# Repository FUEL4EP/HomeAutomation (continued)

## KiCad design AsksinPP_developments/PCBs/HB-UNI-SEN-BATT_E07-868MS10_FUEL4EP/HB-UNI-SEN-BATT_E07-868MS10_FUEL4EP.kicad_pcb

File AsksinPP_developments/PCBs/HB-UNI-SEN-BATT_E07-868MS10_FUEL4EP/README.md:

# HB-UNI-SEN-BATT_E07-868MS10_FUEL4EP  

**Platine für DIY AsksinPP Projekte basierend auf den folgenden möglichen Arduino-Modulen:**
- [Arduino Pro Mini 328 - 3.3V/8MHz](https://www.sparkfun.com/arduino-pro-mini-328-3-3v-8mhz.html): 32kByte Programmspeicher, 4kByte SRAM, 1kByte EEPROM
- NEU: [HB_Pro_Mini_ATMEGA1284P_FUEL4EP](https://github.com/FUEL4EP/HomeAutomation/tree/master/AsksinPP_developments/PCBs/HB_Pro_Mini_ATMEGA1284P_FUEL4EP)
	+ mit deutlich mehr Programm-, RAM- und EEPROM-Speicher als Arduino Pro Mini: 128kByte Programmspeicher, 16kByte SRAM, 4kByte EEPROM)
- [Tindie Pro Mini XL - v2 - ATmega 1284p](https://www.tindie.com/products/prominimicros/pro-mini-xl-v2-atmega-1284p/)
	+ mit deutlich mehr Programm-, RAM- und EEPROM-Speicher als Arduino Pro Mini: 128kByte Programmspeicher, 16kByte SRAM, 4kByte EEPROM)

## Credits

- diese Platine ist von Alexander Reinerts Platine [HB-UNI-SEN-BATT](https://github.com/alexreinert/PCB/tree/master/HB-UNI-SEN-BATT) abgeleitet.
- vielen Dank an Alexander Reinert für die Vorarbeit.

## Status der Validierung der Platine

- Platine wurde bis zur Version V1.3 bei JLCPCB erfolgreich gefertigt und validiert
- der Prototyp der neuen Platinenversion V1.4 wurde bei JLCPCB gefertigt, von Hand bestückt, verlötet und erfolgreich mit dem Sketch [HB-UNI-SENSOR1-AQ-BME680_KF_rLF](https://github.com/FUEL4EP/HomeAutomation/tree/master/AsksinPP_developments/sketches/HB-UNI-Sensor1-AQ-BME680_KF_rLF) validiert:
	
- Als Funkmodul wurde der [Adapter_EByte_E07_900MM10S_to_Ebyte_E07_868MS10_FUEL4EP](https://github.com/FUEL4EP/HomeAutomation/tree/master/AsksinPP_developments/PCBs/Adapter_EByte_E07_900MM10S_to_Ebyte_E07_868MS10_FUEL4EP) verwendet.

## Eigenschaften

- Weiterentwicklung von [HB-UNI-SEN-BATT](https://github.com/alexreinert/PCB/tree/master/HB-UNI-SEN-BATT) mit denselben Außenmaßen
- neue Eigenschaften:
	+ alternativ werden verschiedene Arduino Module unterstützt:
		- [Arduino Pro Mini 328 - 3.3V/8MHz](https://www.sparkfun.com/arduino-pro-mini-328-3-3v-8mhz.html): 32kByte Programmspeicher, 4kByte SRAM, 1kByte EEPROM
		- [HB_Pro_Mini_ATMEGA1284P_FUEL4EP](https://github.com/FUEL4EP/HomeAutomation/tree/master/AsksinPP_developments/PCBs/HB_Pro_Mini_ATMEGA1284P_FUEL4EP)
			+ mit deutlich mehr Programm-, RAM- und EEPROM-Speicher als Arduino Pro Mini: 128kByte Programmspeicher, 16kByte SRAM, 4kByte EEPROM)
			+ mit optionalem Boost-Konverter für Betrieb mit NiMH-Akkumulatoren oder nur einer AA Alkaline Battterie
		- [Tindie Pro Mini XL - v2 - ATmega 1284p](https://www.tindie.com/products/prominimicros/pro-mini-xl-v2-atmega-1284p/)
			+ mit deutlich mehr Programm-, RAM- und EEPROM-Speicher als Arduino Pro Mini: 128kByte Programmspeicher, 16kByte SRAM, 4kByte EEPROM

    + nur eine LED
    + dafür optionale Unterstützung von Akkumulatorbetrieb mit einem externen 'Huckepack' Aufwärtswandlermodul (siehe z.B. [HB-UNI-SENSOR1-CO2-SCD30](https://github.com/FUEL4EP/HomeAutomation/tree/master/AsksinPP_developments/sketches/HB-UNI-Sensor1-CO2_SCD30)
    + Stiftleiste J10 mit Versorgungsspannungen zum Gehäuseoberteil oder Akkulademodul
    + Korrektur der Abstandfehlers bei einem Batteriehalter. Beim [HB-UNI-SEN-BATT](https://github.com/alexreinert/PCB/tree/master/HB-UNI-SEN-BATT) hat das schon mal gerne zu thermischen Ausfällen durch mechanische Spannungen geführt.

### Benötigte Bauteile:
* eines der folgenden Arduino Module
	- [Arduino Pro Mini 328 - 3.3V/8MHz](https://www.sparkfun.com/arduino-pro-mini-328-3-3v-8mhz.html)
	- [HB_Pro_Mini_ATMEGA1284P_FUEL4EP](https://github.com/FUEL4EP/HomeAutomation/tree/master/AsksinPP_developments/PCBs/HB_Pro_Mini_ATMEGA1284P_FUEL4EP)
	- [Tindie Pro Mini XL - v2 - ATmega 1284p](https://www.tindie.com/products/prominimicros/pro-mini-xl-v2-atmega-1284p/)
*  [eByte E07-868MS10 Sendemodul 868MHz](https://www.elecbee.com/de-24376-E07-868MS10-CC1101-Stamp-Hole-Antenna-IoT-UHF-1000m-868MHz-SPI-10dBm-Wireless-Transmitter-Transceiver-RF-Module) oder alternativ das [Elecbee CC1101 Wireless-Modul 868 MHz](https://www.elecbee.com/de-24507-CC1101-Wireless-Module-868MHz-Digital-Transmission-Receiving-Industrial-grade-RF-Communication-Transparent-Transmission) Modul
* 1x LEDs 3mm Low Current (Pin 4)
* 1x 470Ohm Widerstände (Vorwiderstand für LED)
* Elko 10uF 1,5mm
* 2x Keystone 2460 Batteriehalter 1xAA (oder Goobay 1xAA Batteriehalter)
* Mikroschalter 6*6mm
* Stiftleiste RM 1.27mm 1x8 Pin (für eByte E07-868MS10 Modul)
* Stiftleisten RM 2,54mm (nach Bedarf)
* IRLU024N (optional für Verpolungsschutz)
* 100KOhm Widerstand (optional für Verpolungsschutz)
* 2x 10KOhm Widerstand (Pullup für I2C)

### Aufbauhinweise

- es wird dringend angeraten, vor dem Einbau der I2C Sensoren durchzuführen
    + einen Frequenztest. Hier der Frequenztest für einen [Tindie Pro Mini XL - v2 - ATmega 1284p](https://www.tindie.com/products/prominimicros/pro-mini-xl-v2-atmega-1284p/) : [FreqTest_1284P.ino](../Supplements/FreqTest_1284P/FreqTest_1284P.ino)
    + einen Leckstromtest. Hier der Leckstromtest für einen [Tindie Pro Mini XL - v2 - ATmega 1284p](https://www.tindie.com/products/prominimicros/pro-mini-xl-v2-atmega-1284p/) : [SleepTest_1284P.ino](../Supplements/SleepTest_1284P/SleepTest_1284P.ino)
        + der Leckstrom im Sleepmode sollte < 10 uA betragen
    + für einen Arduino Pro Mini die entsprechenden Standardsketche für den Frequenztest und den SleepTest verwenden.
    + am besten diese beiden Tests in einem Testaufbau mit Stecksockeln vor dem Einlöten durchführen

## Konfiguration der Überbrückungen

- bitte die Platinenüberbrückungen vor Inbetriebnahme je nach gewählter Hardwarekonfiguration wählen:

- die Tabellen dazu sind [hier](./Jumper_settings) zu finden
    
## lokale Installation des Github Releases auf Deinem Computer

- gehe bitte in Dein Zielinstallationsverzeichnis, wo Du mit der HB-UNI-SEN-BATT_E07-868MS10_FUEL4EP Platine mit KiCAD arbeiten möchtest

  - gebe dort 'git clone https://github.com/FUEL4EP/HomeAutomation.git' ein
	  + damit lädst Du mein [Sammelrepository](https://github.com/FUEL4EP/HomeAutomation) für alle meine auf Github freigegebenen HomeBrew Entwicklungen herunter.
  - dann findest Du ein neues Verzeichnis 'HomeAutomation' auf Deinem Rechner, das alle meine auf Github freigebenen Entwicklungen enthält, siehe [README.md](https://github.com/FUEL4EP/HomeAutomation/blob/master/README.md)
  	+ mache bitte regelmäßig ein Update mit 'git pull'
 -	die Platine HB-UNI-SEN-BATT_E07-868MS10_FUEL4EP findest Du unter './HomeAutomation/tree/master/AsksinPP_developments/PCBs/HB-UNI-SEN-BATT_E07-868MS10_FUEL4EP'
 
- alternativ kann vom Github [Sammelrepository](https://github.com/FUEL4EP/HomeAutomation) die ZIP-Datei HomeAutomation-master.zip heruntergeladen und auf dem lokalen Rechner ausgepackt werden. Bitte dann regelmäßig auf Github nach Updates schauen.

### Passende AsksinPP Projekte von FUEL4EP
- Arduino Pro Mini ATMega328P oder Tindie Pro Mini XL - v2 - ATmega 1284p basierend:
    + [HB-UNI-Sensor1-THPD-BME280](https://github.com/FUEL4EP/HomeAutomation/tree/master/AsksinPP_developments/sketches/HB-UNI-Sensor1-THPD-BME280)
    + [HB-UNI-Sensor1-TH-SHT75](https://github.com/FUEL4EP/HomeAutomation/tree/master/AsksinPP_developments/sketches/HB-UNI-Sensor1-TH-SHT75)
     + [HB-UNI-Sensor1-CO2_SCD30](https://github.com/FUEL4EP/HomeAutomation/tree/master/AsksinPP_developments/sketches/HB-UNI-Sensor1-CO2_SCD30)
- [HB_Pro_Mini_ATMEGA1284P_FUEL4EP](https://github.com/FUEL4EP/HomeAutomation/tree/master/AsksinPP_developments/PCBs/HB_Pro_Mini_ATMEGA1284P_FUEL4EP) oder [Tindie Pro Mini XL - v2 - ATmega 1284p](https://www.tindie.com/products/prominimicros/pro-mini-xl-v2-atmega-1284p/) basierend:
     + [HB-UNI-Sensor1-AQ-BME680](https://github.com/FUEL4EP/HomeAutomation/tree/master/AsksinPP_developments/sketches/HB-UNI-Sensor1-AQ-BME680)
    + [HB-UNI-Sensor1-AQ-BME680_KF](https://github.com/FUEL4EP/HomeAutomation/tree/master/AsksinPP_developments/sketches/HB-UNI-Sensor1-AQ-BME680_KF)
    + [HB-UNI-Sensor1-AQ-BME680_KF_DEBUG](https://github.com/FUEL4EP/HomeAutomation/tree/master/AsksinPP_developments/sketches/HB-UNI-Sensor1-AQ-BME680_KF_DEBUG)
    + [HB-UNI-Sensor1-RAD-AL53](https://github.com/FUEL4EP/HomeAutomation/tree/master/AsksinPP_developments/sketches/HB-UNI-Sensor1-RAD-AL53)
    + [HB-UNI-Sensor1-THPD-SHT85](https://github.com/FUEL4EP/HomeAutomation/tree/master/AsksinPP_developments/sketches/HB-UNI-Sensor1-THPD-SHT85)

### Passendes Gehäuse
* Camdenboss CBRS01SWH und CBRS01VWH
* oder [Gehäuse HB-UNI-SEN-BATT snap in V2 von wpatrick](https://www.thingiverse.com/thing:3540481) für 3D-Druck

### Hinweise
* Achtung: Kein Überspannungschutz vorhanden
* der Verpolungsschutz ist optional. Dafür Bauteil Q1 (IRLU024N) und R3 (100KOhm Widerstand) bestücken. Alternativ JP1 auf der Platinenrückseite überbrücken, um ohne Verpolungsschutz zu arbeiten.

### KiCAD Plugin
- für die Erzeugung der JLCPCB Produktionsdaten wurde das Plugin [KiCAD JLCPCB tools](https://github.com/bouni/kicad-jlcpcb-tools) verwendet.

## Bestellen von Platinen

- die Platine kann entweder direkt bei JLCPCB bestellt werden
- die notwendigen Produktionsdaten stehen [hier](./jlcpcb/production_files/)
- oder per PN bei [FUEL4EP](https://homematic-forum.de/forum/ucp.php?i=pm&mode=compose&u=20685) im Homematic Forum nachfragen. Aus der Bestellung der Prototypen sind noch Platinen kostengünstig abzugeben (Stand 13. Juli 2023).
	
## passende DIY I2C-Sensormodule für die Fertigung bei JLCPCB
- als DIY-Ersatz für kommerzielle Sensormodule stehen folgende passende Adapterplatinen zur Verfügung:
	- [I2C_Module_BME280_FUEL4EP](https://github.com/FUEL4EP/HomeAutomation/tree/master/AsksinPP_developments/PCBs/I2C_Module_BME280_FUEL4EP)
	- [I2C_Module_BME680_FUEL4EP](https://github.com/FUEL4EP/HomeAutomation/tree/master/AsksinPP_developments/PCBs/I2C_Module_BME680_FUEL4EP)
	- [I2C_Module_SHT85_BME280_FUEL4EP](https://github.com/FUEL4EP/HomeAutomation/tree/master/AsksinPP_developments/PCBs/I2C_Module_SHT85_BME280_FUEL4EP)
	- [I2C_Module_SHT45_BME280_FUEL4EP](https://github.com/FUEL4EP/HomeAutomation/tree/master/AsksinPP_developments/PCBs/I2C_Module_SHT45_BME280_FUEL4EP)
	- [4Bit_I2C_Port_Expander_Module_FUEL4EP](https://github.com/FUEL4EP/HomeAutomation/tree/master/AsksinPP_developments/PCBs/4Bit_I2C_Port_Expander_Module_FUEL4EP)

## Versionen
- KiCad Schaltplan-Editor Version: 8.0.9-8.0.9-0~ubuntu22.04.1, release build unter Kubuntu22.04.1
- KiCad Leiterplatteneditor Version: 8.0.9-8.0.9-0~ubuntu22.04.1, release build unter Kubuntu22.04.1 1.
- aktuelle PCB Version 1.4 
- aktuelle Schematics Version 1.3 

## Disclaimer

-  die Nutzung der hier veröffentlichten Inhalte erfolgt vollständig auf eigenes Risiko und ohne jede Gewähr.

## Lizenz 

**Creative Commons BY-NC-SA**<br>
Give Credit, NonCommercial, ShareAlike

<br />This work is licensed under a <a rel="license" href="http://creativecommons.org/licenses/by-nc-sa/4.0/">Creative Commons Attribution-NonCommercial-ShareAlike 4.0 International License</a>.

-EOF

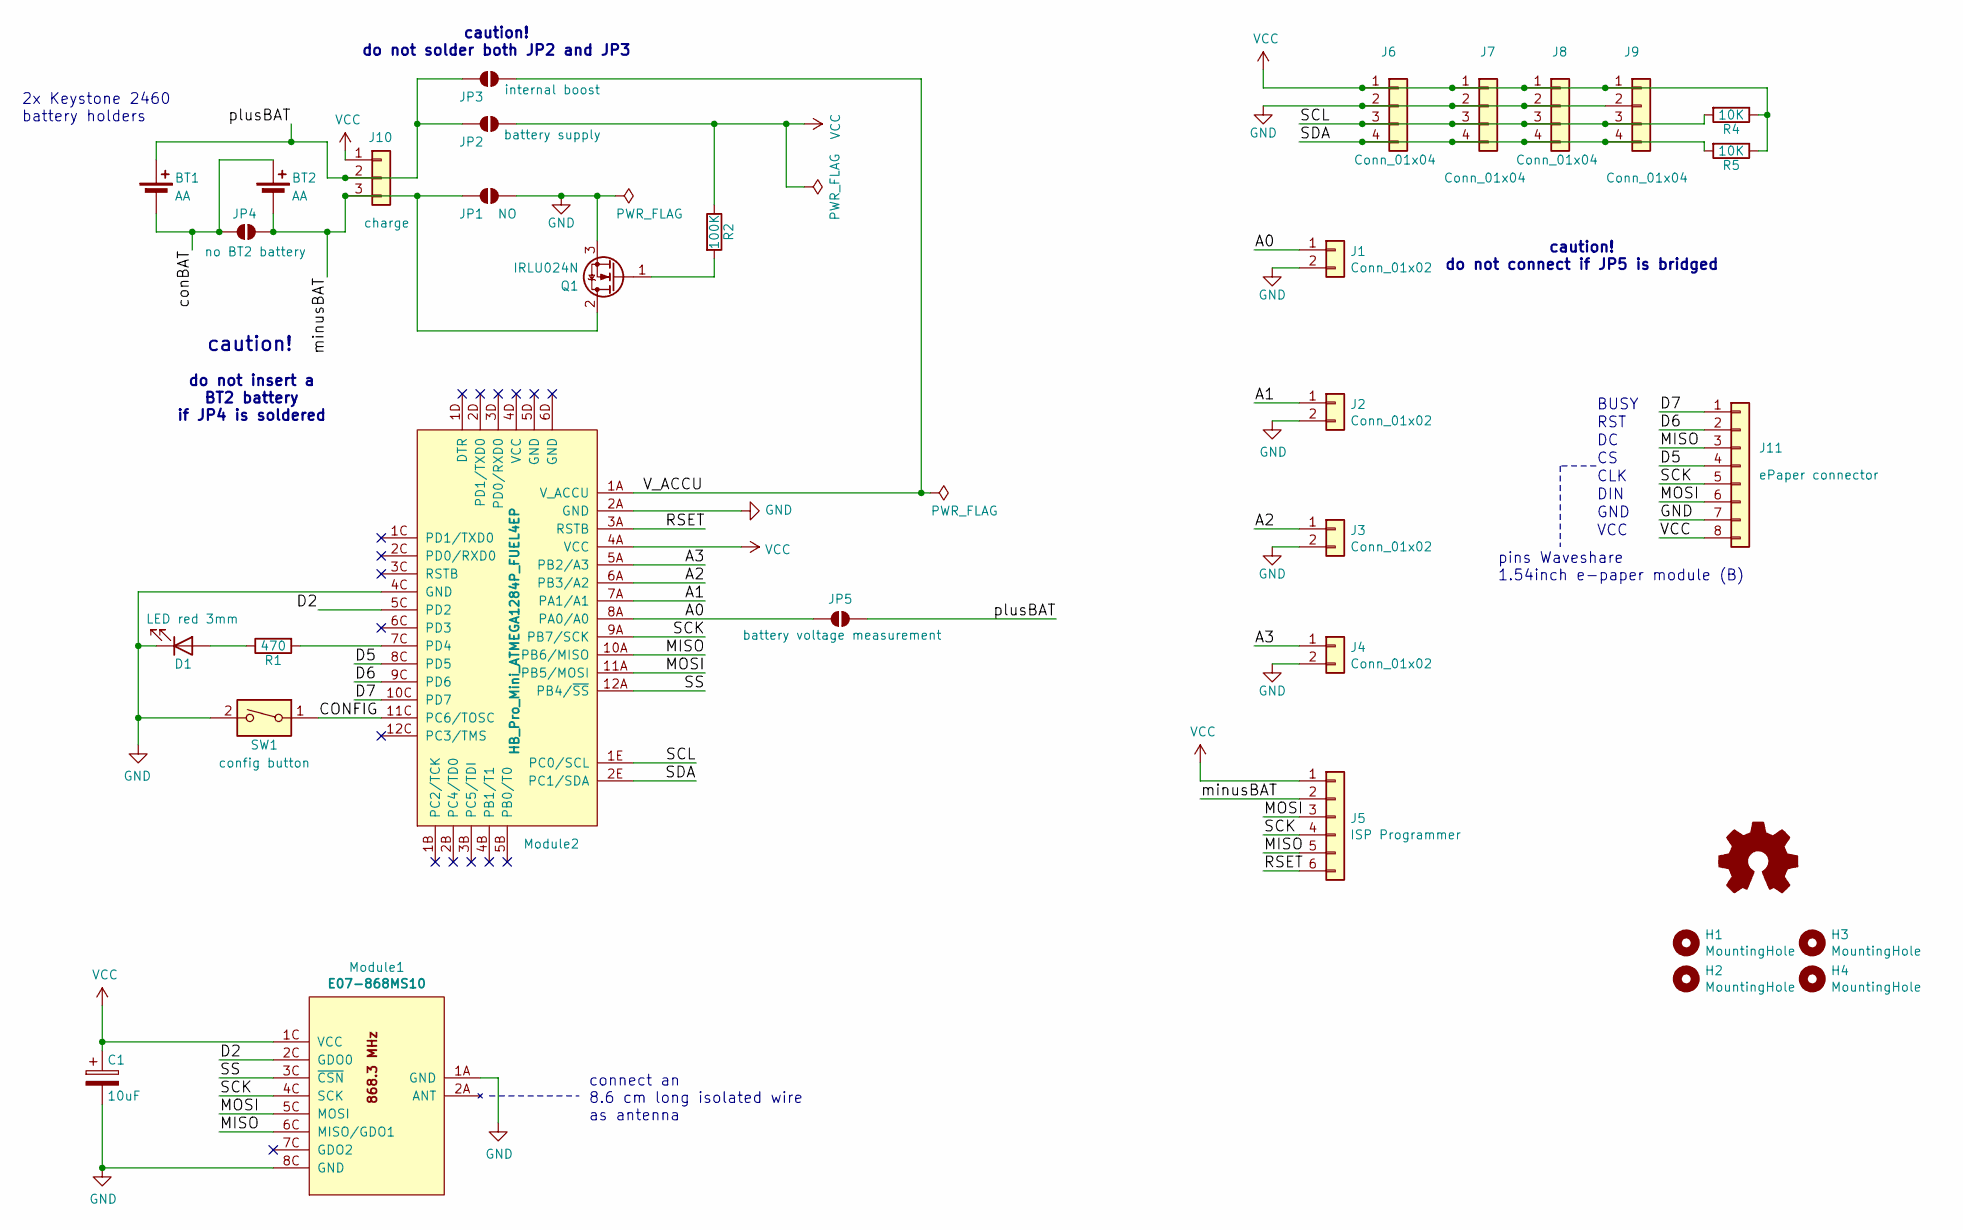
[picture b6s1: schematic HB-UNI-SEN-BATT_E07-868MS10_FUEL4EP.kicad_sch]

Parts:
BT1, BT2: AA; BatteryHolder_Keystone_2460_1xAA
C1: 10uF; CP_Radial_D4.0mm_P1.50mm
D1: LED red 3mm; LED_D3.0mm
H1, H2, H3, H4: MountingHole; MountingHole_2.2mm_M2_Pad_Via
J1, J2, J3, J4: Conn_01x02; PinHeader_1x02_P2.54mm_Vertical
J5: ISP Programmer; PinHeader_1x06_P2.54mm_Vertical
J6, J7, J8, J9: Conn_01x04; PinHeader_1x04_P2.54mm_Vertical
J10: charge; PinHeader_1x03_P2.54mm_Vertical
J11: ePaper connector; PinPads_1x08_P2.00mm_Vertical
JP1: NO; SolderJumper-2_P1.3mm_Open_Pad1.0x1.5mm
JP2: battery supply; SolderJumper-2_P1.3mm_Open_Pad1.0x1.5mm
JP3: internal boost; SolderJumper-2_P1.3mm_Open_Pad1.0x1.5mm
JP4: no BT2 battery; SolderJumper-2_P1.3mm_Open_Pad1.0x1.5mm
JP5: battery voltage measurement; SolderJumper-2_P1.3mm_Open_Pad1.0x1.5mm
LOGO1: Logo_Open_Hardware_Small; CC-BY-ND-SA
Module1: E07-868MS10; eByte_E07-868MS10
Module2: HB_Pro_Mini_ATMEGA1284P_FUEL4EP
Q1: IRLU024N; TO-251-3_Vertical
R1: 470; R_Axial_DIN0207_L6.3mm_D2.5mm_P2.54mm_Vertical
R2: 100K; R_Axial_DIN0207_L6.3mm_D2.5mm_P2.54mm_Vertical
R4, R5: 10K; R_Axial_DIN0207_L6.3mm_D2.5mm_P2.54mm_Vertical
SW1: config button; SW_PUSH_6mm_H5mm

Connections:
/A0: J1.1, JP5.1 (A), Module2.8A (PA0/A0)
/A1: J2.1, Module2.7A (PA1/A1)
/A2: J3.1, Module2.6A (PB3/A2)
/A3: J4.1, Module2.5A (PB2/A3)
/CONFIG: Module2.11C (PC6/TOSC), SW1.1
/D2: Module1.2C (GDO0), Module2.5C (PD2)
/D5: J11.4, Module2.8C (PD5)
/D6: J11.2, Module2.9C (PD6)
/D7: J11.1, Module2.10C (PD7)
/MISO: J5.5, J11.3, Module1.6C (MISO/GDO1), Module2.10A (PB6/MISO)
/MOSI: J5.3, J11.6, Module1.5C (MOSI), Module2.11A (PB5/MOSI)
/RSET: J5.6, Module2.3A (RSTB)
/SCK: J5.4, J11.5, Module1.4C (SCK), Module2.9A (PB7/SCK)
/SCL: J6.3, J7.3, J8.3, J9.3, Module2.1E (PC0/SCL), R4.2
/SDA: J6.4, J7.4, J8.4, J9.4, Module2.2E (PC1/SDA), R5.2
/SS: Module1.3C (~CSN), Module2.12A (PB4/~SS)
/V_ACCU: JP3.2 (B), Module2.1A (V_ACCU)
/conBAT: BT1.2 (-), BT2.1 (+), JP4.1 (A)
/minusBAT: BT2.2 (-), J5.2, J10.3, JP1.1 (A), JP4.2 (B), Q1.2 (D)
/plusBAT: BT1.1 (+), J10.2, JP2.1 (A), JP3.1 (A), JP5.2 (B)
GND: C1.2, D1.1 (K), J1.2, J2.2, J3.2, J4.2, J6.2, J7.2, J8.2, J9.2, J11.7, JP1.2 (B), Module1.1A (GND), Module1.8C (GND), Module2.2A (GND), Module2.4C (GND), Q1.3 (S), SW1.2
unnamed: D1.2 (A), R1.1
unnamed: Module2.7C (PD4), R1.2
unnamed: Q1.1 (G), R2.2
VCC: C1.1, J5.1, J6.1, J7.1, J8.1, J9.1, J10.1, J11.8, JP2.2 (B), Module1.1C (VCC), Module2.4A (VCC), R2.1, R4.1, R5.1

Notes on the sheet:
VCC
DIN
connect an 8.6 cm long isolated wire as antenna
BUSY
2x Keystone 2460 battery holders
GND
CLK
caution! do not connect if JP5 is bridged
caution!
RST
do not insert a BT2 battery if JP4 is soldered
caution! do not solder both JP2 and JP3
pins Waveshare 1.54inch e-paper module (B)

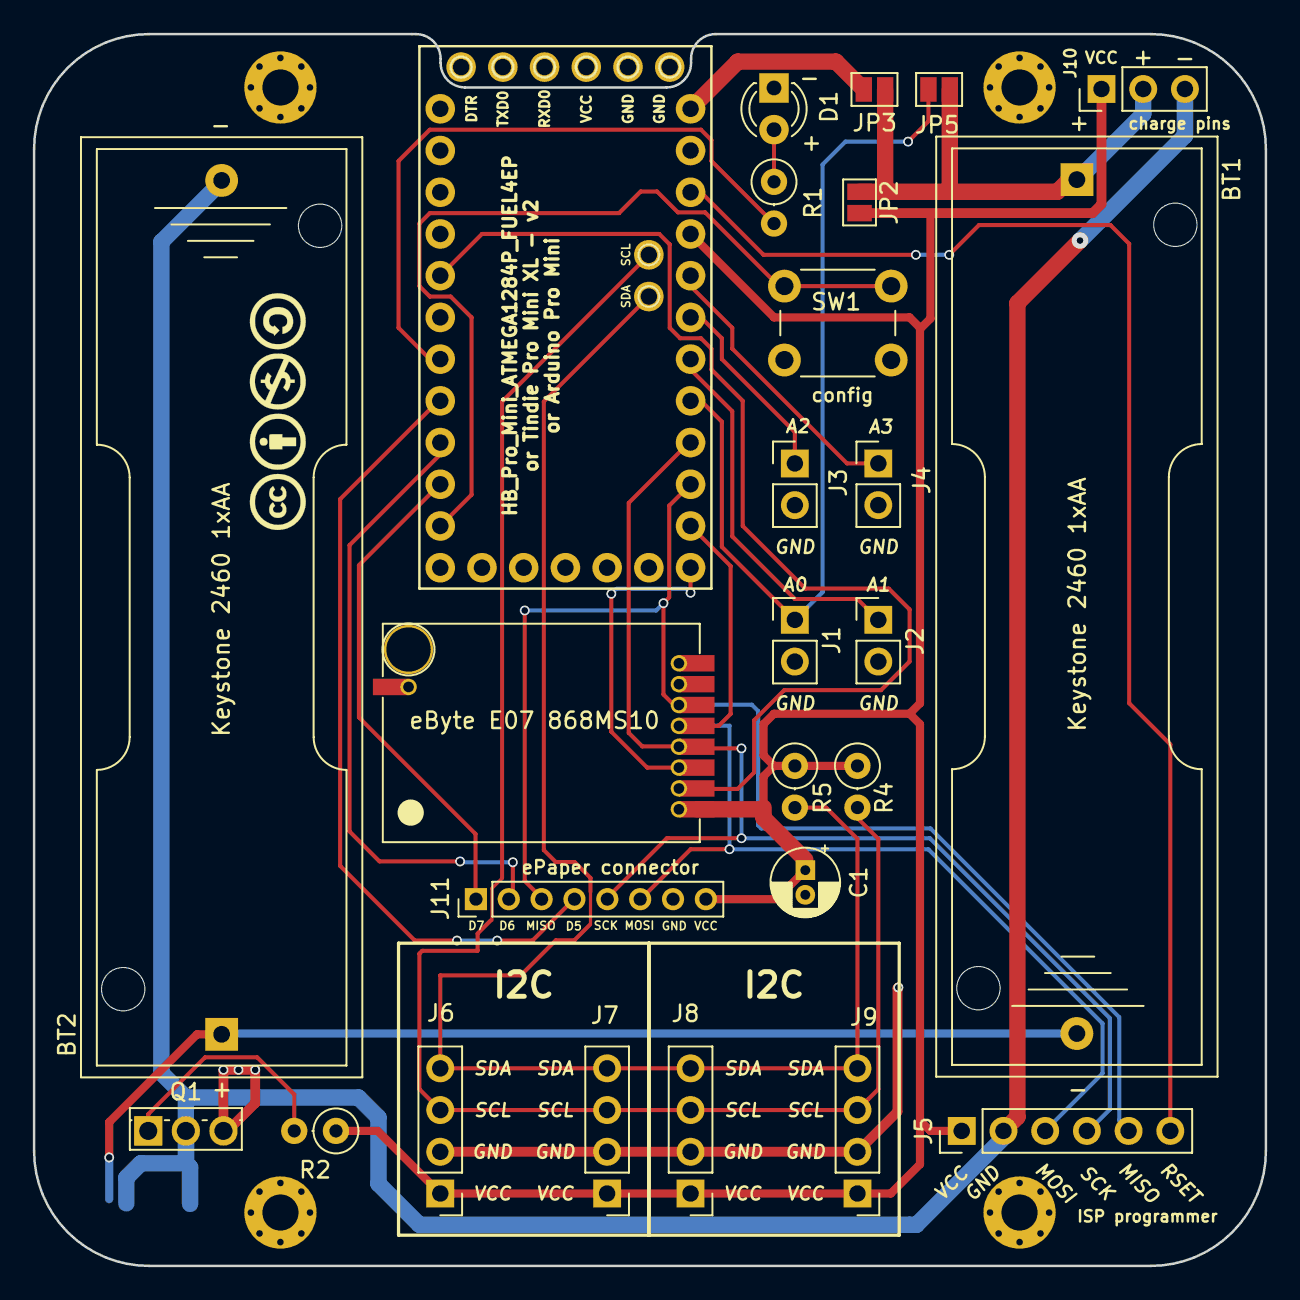
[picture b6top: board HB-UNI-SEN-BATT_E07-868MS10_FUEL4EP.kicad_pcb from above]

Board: 2 copper layers, 75.0 x 75.0 mm, 33 parts (0 on the bottom side), 25 nets.

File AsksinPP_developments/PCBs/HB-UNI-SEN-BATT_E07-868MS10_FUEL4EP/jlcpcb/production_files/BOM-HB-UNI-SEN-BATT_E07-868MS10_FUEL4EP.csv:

Comment,Designator,Footprint,LCSC,Quantity
LED red 3mm,D1,LED_D3.0mm,,1
Conn_01x02,J1,PinHeader_1x02_P2.54mm_Vertical,,1
Conn_01x02,J2,PinHeader_1x02_P2.54mm_Vertical,,1
Conn_01x04,J7,PinHeader_1x04_P2.54mm_Vertical,,1
AA,BT1,BatteryHolder_Keystone_2460_1xAA,,1
Conn_01x02,J3,PinHeader_1x02_P2.54mm_Vertical,,1
Conn_01x02,J4,PinHeader_1x02_P2.54mm_Vertical,,1
ISP Programmer,J5,PinHeader_1x06_P2.54mm_Vertical,,1
Conn_01x04,J6,PinHeader_1x04_P2.54mm_Vertical,,1
10uF,C1,CP_Radial_D4.0mm_P1.50mm,,1
10K,R4,R_Axial_DIN0207_L6.3mm_D2.5mm_P2.54mm_Vertical,,1
10K,R5,R_Axial_DIN0207_L6.3mm_D2.5mm_P2.54mm_Vertical,,1
470,R1,R_Axial_DIN0207_L6.3mm_D2.5mm_P2.54mm_Vertical,,1
IRLU024N,Q1,TO-251-3_Vertical,,1
Conn_01x04,J9,PinHeader_1x04_P2.54mm_Vertical,,1
charge,J10,PinHeader_1x03_P2.54mm_Vertical,,1
NO,JP1,SolderJumper-2_P1.3mm_Open_Pad1.0x1.5mm,,1
HB_Pro_Mini_ATMEGA1284P_FUEL4EP,Module2,HB_Pro_Mini_ATMEGA1284P_FUEL4EP,,1
E07-868MS10,Module1,eByte_E07-868MS10,,1
battery supply,JP2,SolderJumper-2_P1.3mm_Open_Pad1.0x1.5mm,,1
config button,SW1,SW_PUSH_6mm_H5mm,,1
Conn_01x04,J8,PinHeader_1x04_P2.54mm_Vertical,,1
MountingHole,H2,MountingHole_2.2mm_M2_Pad_Via,,1
MountingHole,H4,MountingHole_2.2mm_M2_Pad_Via,,1
MountingHole,H1,MountingHole_2.2mm_M2_Pad_Via,,1
MountingHole,H3,MountingHole_2.2mm_M2_Pad_Via,,1
Logo_Open_Hardware_Small,LOGO1,CC-BY-ND-SA,,1
ePaper connector,J11,PinPads_1x08_P2.00mm_Vertical,,1
AA,BT2,BatteryHolder_Keystone_2460_1xAA,,1
100K,R2,R_Axial_DIN0207_L6.3mm_D2.5mm_P2.54mm_Vertical,,1
battery voltage measurement,JP5,SolderJumper-2_P1.3mm_Open_Pad1.0x1.5mm,,1
no BT2 battery,JP4,SolderJumper-2_P1.3mm_Open_Pad1.0x1.5mm,,1
internal boost,JP3,SolderJumper-2_P1.3mm_Open_Pad1.0x1.5mm,,1

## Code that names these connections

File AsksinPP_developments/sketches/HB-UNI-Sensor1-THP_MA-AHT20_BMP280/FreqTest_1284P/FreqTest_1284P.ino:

//- -----------------------------------------------------------------------------------------------------------------------
// AskSin++
// 2016-10-31 papa Creative Commons - http://creativecommons.org/licenses/by-nc-sa/3.0/de/
// 2019-11-16 stan23 Creative Commons - http://creativecommons.org/licenses/by-nc-sa/3.0/de/
//- -----------------------------------------------------------------------------------------------------------------------

// define this to read the device id, serial and device type from bootloader section
// #define USE_OTA_BOOTLOADER

#define ATMega1284P

#if defined ARDUINO_ARCH_STM32F1
  #define STORAGEDRIVER at24cX<0x50,128,32>
  #define TICKS_PER_SECOND 500UL
  #define USE_HW_SERIAL
 
  #include <SPI.h>    // when we include SPI.h - we can use LibSPI class
  #include <Wire.h>   // for I2C access to EEPROM
  #include <EEPROM.h> // the EEPROM library contains Flash Access Methods
#endif

#include <AskSinPP.h>
#include <Device.h>
#include <Register.h>


#if defined ARDUINO_ARCH_STM32F1
  // we use a BluePill
  #define CC1101_GDO0_PIN     PB0
  #define CC1101_CS_PIN       PA4
  // CC1101 communication uses HW-SPI
  #define LED_PIN             LED_BUILTIN
#endif
#if defined ATMega1284P
// we use a ATMega 1284p Pro Mini XL
  #define CC1101_CS_PIN       4     // PB4
  #define CC1101_GDO0_PIN     10    // PD2
  #define CC1101_SCK_PIN      7     // PB7
  #define CC1101_MOSI_PIN     5     // PB5
  #define CC1101_MISO_PIN     6     // PB6
// ATMega 1284p LED
 #define LED_PIN             12     // PD4
#else
// we use a Pro Mini  
  #define CC1101_GDO0_PIN     2     // PD2
  #define CC1101_CS_PIN       10    // PB2
  #define CC1101_MOSI_PIN     11    // PB3
  #define CC1101_MISO_PIN     12    // PB4
  #define CC1101_SCK_PIN      13    // PB5
  // Pro Mini LED
  #define LED_PIN             4     // PD4
#endif

// all library classes are placed in the namespace 'as'
using namespace as;

// define all device properties
const struct DeviceInfo PROGMEM devinfo = {
    {0x01,0x01,0x01},       // Device ID
    "FreqTest00",           // Device Serial
    {0x00,0x00},            // Device Model
    0x10,                   // Firmware Version
    as::DeviceType::Sensor, // Device Type
    {0x00,0x00}             // Info Bytes
};

/**
 * Configure the used hardware
 */
#if defined ARDUINO_ARCH_STM32F1
typedef LibSPI<CC1101_CS_PIN> RadioSPI;
#else
//typedef AvrSPI<CC1101_CS_PIN, CC1101_MOSI_PIN, CC1101_MISO_PIN, CC1101_SCK_PIN> RadioSPI;
typedef AvrSPI<CC1101_CS_PIN, CC1101_MOSI_PIN, CC1101_MISO_PIN, CC1101_SCK_PIN> SPIType;
#endif
//typedef Radio<RadioSPI, CC1101_GDO0_PIN> RadioType;
typedef Radio<SPIType, CC1101_GDO0_PIN> RadioType;
typedef StatusLed<LED_PIN> LedType;
typedef AskSin<LedType,NoBattery,RadioType> HalType;



#define STARTFREQ 0x656A             // frequency we start scanning
#define MINFREQ (STARTFREQ - 0x300)  // frequency we abort scanning
#define SEARCHSTEP 0x50              // step with during search
#define BOUNDSTEP 0x10               // step width during upper/lower bound analysis


// see https://github.com/AskSinPP/asksinpp.de/blob/master/Grundlagen/FAQ/Fehlerhafte_CC1101.md
//#define ACTIVE_PING
HMID PING_FROM(0x6D,0xCC,0xC5);      // from address for status message e.g. switch
HMID PING_TO(0x19,0x57,0x4d);        // to address for status message / central / CCU
#ifdef ACTIVE_PING
  #define SCANTIME seconds2ticks(5)  // maximal time to wait for a valid message
#else
  #define SCANTIME seconds2ticks(60) // maximal time to wait for a valid message
#endif



class TestDevice : public Device<HalType,DefList0>, Alarm {
  DefList0 l0;
  uint16_t freq, start, end;
  uint8_t received, rssi;
public:
  enum SearchMode { Search, Up, Down, Done };
  SearchMode mode;
  HMID id;

  typedef Device<HalType,DefList0> BaseDevice;
  TestDevice (const DeviceInfo& i,uint16_t addr) : BaseDevice(i,addr,l0,0), Alarm(0), l0(addr),
      freq(STARTFREQ), start(STARTFREQ), end(STARTFREQ),
      received(0), rssi(0), mode(Search)  {}
  virtual ~TestDevice () {}

  virtual void trigger (__attribute__ ((unused)) AlarmClock& clock) {
    DPRINT("  ");DDEC(received);
    if (!received) {
      DPRINTLN("");
    } else {
      DPRINT(" / -");DDEC(rssi);DPRINTLN("dBm");
    }

    if( mode == Search ) {
      if( received > 0 ) {
        start = end = freq;
        mode = Up; // start find upper bound
        DPRINTLN("Search for upper bound");
        setFreq(freq + BOUNDSTEP);
      }
      else {
        if( freq < MINFREQ ) mode = Done;
        if( freq <= STARTFREQ ) setFreq(STARTFREQ + (STARTFREQ-freq) + SEARCHSTEP);
        else setFreq(STARTFREQ - (freq-STARTFREQ));
      }
    }
    else if(mode == Up) {
      if( received > 0 ) {
        end = freq;
        setFreq(end + BOUNDSTEP);
      }
      else {
        mode = Down; // start find lower bound
        DPRINTLN("Search for lower bound");
        setFreq(start - BOUNDSTEP);
      }
    }
    else if(mode == Down) {
      if( received > 0 ) {
        start = freq;
        setFreq(start - BOUNDSTEP);
      }
      else {
        mode = Done;
      }
    }
    if( mode == Done ) {
      DPRINT("\nDone: 0x21");DHEX(start);DPRINT(" - 0x21");DHEXLN(end);
      if( start == end && start == STARTFREQ ) {
        DPRINT("Could not receive any message");
      }
      else {
        freq = start+((end - start)/2);
        DPRINT("Calculated Freq: 0x21");DHEX((uint8_t)(freq>>8));DHEX((uint8_t)(freq&0xff));
        printFreq(0x210000 + freq);DPRINTLN("");

        // store frequency
        DPRINT("Store into config area: ");DHEX((uint8_t)(freq>>8));DHEX((uint8_t)(freq&0xff));
        StorageConfig sc = getConfigArea();
#if defined ARDUINO_ARCH_STM32F1
        Wire.begin();
        DPRINT(".");
#endif
        sc.clear();
        DPRINT(".");
        sc.setByte(CONFIG_FREQ1, freq>>8);
        DPRINT(".");
        sc.setByte(CONFIG_FREQ2, freq&0xff);
        DPRINT(".");
        sc.validate();

        DPRINTLN("stored!");
#if defined ARDUINO_ARCH_STM32F1
        // measurement is done, loop here forever
        while(1);
#else
        activity().savePower<Sleep<> >(this->getHal());
#endif
      }
    }
  }

  virtual bool process(Message& msg) {
    msg.from().dump(); DPRINT(".");
    rssi = max(rssi,radio().rssi());
    received++;
    if( received > 0 ) {
      trigger(sysclock);
    }
    return true;
  }

  bool init (HalType& hal) {
    this->setHal(hal);
    this->getDeviceID(id);
    hal.init(id);

    DPRINTLN("Start searching ...");
    setFreq(STARTFREQ);
    return false;
  }

  void setFreq (uint16_t current) {
    sysclock.cancel(*this);
    freq = current;
    rssi=0;
    received=0;
    DPRINT("Freq 0x21");DHEX(freq);
    printFreq(0x210000 + freq);
    DPRINT(": ");
    this->radio().initReg(CC1101_FREQ2, 0x21);
    this->radio().initReg(CC1101_FREQ1, freq >> 8);
    this->radio().initReg(CC1101_FREQ0, freq & 0xff);
    set(SCANTIME);
    sysclock.add(*this);
  }

  void printFreq(uint32_t freq) {
    char buffer[16];
    float val = (float)freq * 26.0 / 65536.0;
    dtostrf(val, 8, 3, buffer);
    DPRINT(buffer);DPRINT(" MHz");
  }
};

HalType hal;
TestDevice sdev(devinfo,0x20);

class InfoSender : public Alarm {
  class channel {
  public:
    uint8_t number() const {return 1; }
    uint8_t status() const {return 0; }
    uint8_t flags()  const {return 0; }
    void patchStatus(__attribute__ ((unused)) Message& msg) {}
    void changed(__attribute__ ((unused)) bool b) {}
  };
  uint8_t cnt;
  channel ch;
public:
  InfoSender () : Alarm(0), cnt(0) {}
  virtual ~InfoSender () {}

  virtual void trigger (AlarmClock& clock) {
#ifdef ACTIVE_PING
    InfoActuatorStatusMsg msg;
    msg.init(cnt++, ch, hal.radio.rssi());
    msg.to(PING_TO);
    msg.from(PING_FROM);
    msg.ackRequired();
    msg.setRpten();
    sdev.radio().write(msg,msg.burstRequired());
#endif
    sdev.led().ledOn(millis2ticks(100), 0);
    if( sdev.mode != TestDevice::SearchMode::Done ) {
      set(seconds2ticks(1));
      clock.add(*this);
    }
  }
} info;

void setup () {
#if defined ARDUINO_ARCH_STM32F1
  delay(5000);
#endif
  DINIT(38400,ASKSIN_PLUS_PLUS_IDENTIFIER);
  sdev.init(hal);
  // start sender
  info.trigger(sysclock);
}

void loop() {
  sdev.pollRadio();
  hal.runready();
}

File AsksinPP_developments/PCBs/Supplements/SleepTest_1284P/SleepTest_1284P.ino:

// ~~~~~~~~~~~~~~~~~~~~~~~~~~~~~~~~~~~~~~~~~~~~~~~~~~~~~~~~
// SleepTest (AVR Power-down Mode)
// 2019-01-22 Tom Major (Creative Commons)
// https://creativecommons.org/licenses/by-nc-sa/3.0/
// Clock Fuses: RC-Oszillator 8MHz, BOD off
// alternativ 8MHz Quarz an XTAL
//
// Der AVR wechselt mit diesem Sketch zwischen 10sec Aktiv Mode und 8sec power-down Mode mit Watchdog wakeup
// !! Falls mit der HW alles stimmt benötigt die Schaltung im power-down Mode nur ca. 4uA !!
//
// Auf die uA-Messung sollte man nur dann kurz umschalten wenn der AVR im power-down Mode ist (LED aus) und vor Ablauf der 8sec
// wieder zurück auf den mA-Messbereich. Andernfalls wird der AVR im aktivem Zustand eventuell nicht wieder anlaufen, da der Spannungsabfall
// dann über den uA-Messbereich des Multimeters zu hoch ist.
// ~~~~~~~~~~~~~~~~~~~~~~~~~~~~~~~~~~~~~~~~~~~~~~~~~~~~~~~~

#include <SPI.h>
#include "LowPower.h"

#define Tindie_m1284p

const int ledPin = 12;

void setup() 
{
    // cc1101_powerdown nur aktivieren falls wirklich ein CC1101 angeschlossen ist!
    cc1101_powerdown();
    pinMode(ledPin, OUTPUT);
}

void loop() 
{
    digitalWrite(ledPin, HIGH);
    delay(4000); 
    digitalWrite(ledPin, LOW);
    LowPower.powerDown(SLEEP_8S, ADC_OFF, BOD_OFF);  
}

// -------------------------------------------------------------------------
// CC1101 power down

#if defined Tindie_m1284p
  #define CC1101_GDO0        10           // PD2
  #define CC1101_CS_PIN       4           // PB4
#else // ATMega328P
  #define CC1101_GDO0         2           // GDO0 input interrupt pin
  #define CC1101_CS_PIN      10           // PB2
#endif

#define CC1101_SRES         0x30        // Reset CC1101 chip
#define CC1101_SIDLE        0x36        // Exit RX / TX, turn off frequency synthesizer and exit Wake-On-Radio mode if applicable
#define CC1101_SPWD         0x39        // Enter power down mode when CSn goes high

#define cc1101_Select()     digitalWrite(CC1101_CS_PIN, LOW)
#define cc1101_Deselect()   digitalWrite(CC1101_CS_PIN, HIGH)
#define wait_Miso()         while(digitalRead(MISO)>0)

void cc1101_powerdown()
{
  SPI.begin();                          // Initialize SPI interface
  pinMode(CC1101_GDO0, INPUT);          // Config GDO0 as input

  //reset();                            // Reset CC1101
  cc1101_Deselect();                    // Deselect CC1101
  delayMicroseconds(5);
  cc1101_Select();                      // Select CC1101
  delayMicroseconds(10);
  cc1101_Deselect();                    // Deselect CC1101
  delayMicroseconds(41);
  cc1101_Select();                      // Select CC1101

  wait_Miso();                          // Wait until MISO goes low
  SPI.transfer(CC1101_SRES);            // Send reset command strobe
  wait_Miso();                          // Wait until MISO goes low

  cc1101_Deselect();                    // Deselect CC1101
  // reset() end

  delay(100);
  
  //cmdStrobe(byte cmd) 
  cc1101_Select();                      // Select CC1101
  wait_Miso();                          // Wait until MISO goes low
  SPI.transfer(CC1101_SIDLE);           // Send strobe command
  cc1101_Deselect();                    // Deselect CC1101
  
  //cmdStrobe(byte cmd) 
  cc1101_Select();                      // Select CC1101
  wait_Miso();                          // Wait until MISO goes low
  SPI.transfer(CC1101_SPWD);            // Send strobe command
  cc1101_Deselect();                    // Deselect CC1101

  SPI.end();
  delay(10);
}

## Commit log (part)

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2021-11-25 HB-UNI-Sensor1-RAD-AL53: Some documentation updates, PCBs/HB-UNI-SenAct-4-4-SC_DS_FUEL4EP and PCBs/HM-LC-Bl1-FM_FUEL4EP: BOM lists
2021-12-08 HB-UNI-Sensor1-THPD-SHT85: added new option for calculating moving averages for temperature over 24h and 7days (requires an ATMega1284P); still under validation
2021-12-09 HB-UNI-Sensor1-THPD-SHT85: Added calibration of SYSCLOCK
2021-12-22 PCBs/HB-UNI-SenAct-4-4-SC_DS_FUEL4EP and PCBs/HM-LC-Bl1-FM_FUEL4EP: fixes of some geometry flaws that popped up during trial assembly
2021-12-27 PCBs/HM-LC-Bl1-FM_FUEL4EP and PCBs/HB-UNI-SenAct-4-4-SC_DS_FUEL4EP: fixes, new V1.2 PCB layouts
2022-01-02 PCBs/HM-LC-Bl1-FM_FUEL4EP: fix of a wrong symbol
2022-01-08 added AsksinPP_developments/tools/tmBattery_tmBatteryResDiv_calculator.ods for Libreoffice Calc
2022-01-10 PCBs/HB-UNI-SEN-BATT_ATMega1284P_E07-868MS10_FUEL4EP and PCBs/HB-UNI-SEN-BATT_ATMega1284P_E07-868MS10_FRAM_FUEL4EP: changed R8 from 200kOhm to 47kOhm for better measurement accuracy
2022-02-01 HB-UNI-Sensor1-TH-SHT75: added 24h moving average (option); HB-UNI-Sensor1-THPD-SHT85: increased resolution of moving average filters to 0.1 K; HB-UNI-Sensor1-AQ-BME680_KF: improved Python scripts; h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
2022-03-06 hb-ep-devices-addon: don't increase VERSION (yet)
2022-04-15 HB-UNI-Sensor1-TH-SHT75 and HB-UNI-Sensor1-RAD-AL53: documentation updates
2022-08-01 HB-UNI-Sensor1-RAD-AL53: additional measurement results, accumulator voltage histogram over 3 months
2022-08-01 HB-UNI-Sensor1-AQ-BME680_KF_DEBUG and HB-UNI-Sensor1-AQ-BME680: reduced BAT_VOLT_LOW to 2.7V and BAT_VOLT_CRITICAL to 2.6V
2022-08-01 HB-UNI-Sensor1-RAD-AL53: fixed file name
2022-08-10 HB-UNI-Sensor1-RAD-AL53: Added example scripts of a push alarm by ProwlApp on iPhone or iPad
2022-08-10 HB-UNI-Sensor1-RAD-AL53/ProwlApp_Alarm/Readme.md: fix of typos
2022-08-19 added ko-fi donation possibility to README.md
2022-08-19 fix of format errors
2022-09-08 HB-UNI-Sensor1-RAD-AL53: added measurement results of para nuts / update of README.md
2022-09-11 HB-UNI-Sensor1-RAD-AL53: added some additional description for radon measurements
2022-09-15 HB-UNI-Sensor1-RAD-AL53: improved Miele_vacuum_clearer_adapter_for_radon_fission_product_collector / update of README.md
2022-09-21 HB-UNI-Sensor1-RAD-AL53: added comparison of radon measurement between cellar and living room
2022-10-10 HB-UNI-Sensor1-RAD-AL53: Update of README.md
2022-10-20 HB-UNI-Sensor1-RAD-AL53: added radon measurement result of an Airthings Corentium Home measuring device
2023-03-26 HB-UNI-Sensor1-RAD-AL53: update of README.md; updated accumulator discharge time to 6+ months
2023-05-10 HB-UNI-SenAct-4-4-SC_DS_FUEL4EP: Added STL files for a 3D printable case
2023-05-12 added AsksinPP_developments/tools/tmBattery_tmBatteryResDiv_calculator.xlsx
2023-07-16 README.md: fixes and additions
2023-07-17 HB-UNI-SenAct-4-4-SC_DS_FUEL4EP: added pictures
2023-07-17 HB-UNI-SenAct-4-4-SC_DS: Add patch for AsksinPP/Radio.h
2023-07-18 HB-UNI-SenAct-4-4-SC_DS_FUEL4EP, HM-LC-Bl1-FM_FUEL4EP, and HB-UNI-Sensor1-AQ-BME680_KF_rLF: some minor updates
2023-07-20 README.md updates / source for E07-868MS10 module
2023-07-25 HB-UNI-SenAct-4-4-SC_DS and HB-UNI-SenAct-4-4-SC_DS_FUEL4EP: update of README.md; update and deletion of some JLCPCB production related files
2023-07-28 HM-LC-Bl1-FM_FUEL4EP and HB-UNI-SenAct-4-4-SC_DS_FUEL4EP: fix of MCP1702 from 2.8V to 3.3V version
2023-07-29 PCB HB-UNI-SenAct-4-4-SC_DS_FUEL4EP: update of 3D print case / increased size of battery pack box
2023-08-04 hb-ep-devices-addon: upgrade to V1.15; HB-UNI-SenAct-4-4-RC_DS: new sketch; HB-UNI-SenAct-4-4-SC_DS: fix of sketch
2023-08-04 hb-ep-devices-addon: fix of device name
2023-08-14 HB-UNI-SenAct-4-4-SC_DS_FUEL4EP: add supressor capacitor; documentation updates
2023-08-15 HB-UNI-SEN-BATT_ATMega1284P_E07-868MS10_FUEL4EP: delete wrong directory
2023-08-25 PCBs: added CC1101_868MHz_RF_Modul_FUEL4EP; note: not yet validated!
2023-08-27 PCBs: CC1101_868MHz_RF_Modul_FUEL4EP and CC1101_868MHz_UFL_RF_Modul_FUEL4EP: improvements suggested by ivo
2023-09-01 PCBs: CC1101_868MHz_RF_Modul_FUEL4EP, CC1101_868MHz_UFL_RF_Modul_FUEL4EP: update of silkscreen texts
2023-09-03 PCBs: added 4Bit_I2C_Port_Expander_Module_FUEL4EP
2023-09-03 fixed filename
2023-09-07 PCBs: I2C_Module_BME280_FUEL4EP and I2C_Module_BME680_FUEL4EP: updated LCSC numberss for assembly at JLCPCB
2023-09-09 PCBs: added I2C_Module_SHT45_BME280_FUEL4EP
2023-09-11 PCBs/HB-UNI-SEN-BATT_E07-900MM10S_FUEL4EP: update of README.md
2023-09-11 PCBs/HB-UNI-SEN-BATT_E07-900MM10S_FUEL4EP: updated 3D view
2023-09-13 PCBs: added HB-UNI-SEN-BATT_ATMega1284P_E07-900MM10S_FUEL4EP; fies fixes for HB-UNI-SEN-BATT_ATMega1284P_E07-868MS10_FUEL4EP and HB-UNI-SEN-BATT_E07-900MM10S_FUEL4EP
2023-09-21 PCBs: CC1101_868MHz_UFL_RF_Modul_FUEL4EP: derivated from CC1101_868MHz_RF_Modul_FUEL4EP with improved decoupling capacitor return paths
2023-11-24 HB-UNI-Sensor1-AQ-BME680_KF_rLF: Update of README.md
2023-12-15 PCBs: HB_TH_Sensor_SHT45_AllInOne_FUEL4EP and I2C_Module_SHT45_BME280_FUEL4EP: replacement of SHT45 to type without PTFE filter
2024-01-07 PCBs: Updates due to order of some prototypes at JLCPCB
2024-01-13 PCBs: HB_TH_Sensor_SHT45_AllInOne_FUEL4EP (updates), added HB_Stamp_ATMega1284P_FUEL4EP and I2C_Module_SHT45_BME280_small_FUEL4EP
2024-01-15 PCBs: HB_Stamp_ATMega1284P_FUEL4EP and I2C_Module_SHT45_BME280_small_FUEL4EP: make I2C sockets fitting each other
2024-01-21 PCBs: updates of HB_TH_Sensor_SHT45_AllInOne_FUEL4EP and HB_Stamp_ATMega1284P_FUEL4EP see README.mds
2024-02-09 PCBs: fix of I2C Pull-up resistors that were wrongly tied to GND
2024-02-14 PCBs: I2C_Module_SHT45_BME280_small_FUEL4EP: shrinked x-size to 14.08 mm for geeting space for pogo-pin-adapter at mother board
2024-02-14 hb-ep-devices-addon V1.16 / added 2 new Sensirioon SHT45 based Asksinpp sensors
2024-02-14 intermediate documentation update for new sensors
2024-02-15 PCBs/HB_TH_Sensor_SHT45_AllInOne_FUEL4EP and sketches/HB-UNI-Sensor1-THD-SHT45: documentation updates
2024-02-16 HB_Stamp_ATMega1284P_FUEL4EP: documentation updates
2024-02-16 PCBs/I2C_Module_SHT45_BME280_small_FUEL4EP: documentation update
2024-02-17 PCBs: fixed documentation for tmBatteryResDiv / activations pin names were wrong
2024-02-18 HB-UNI-Sensor1-THPD-SHT45_BME280: documentation updates
2024-03-06 updated documentation (case for HB-UNI-Sensor1-THPD-SHT45_BME280)
2024-03-06 case_HB-UNI-Sensor1-THPD-SHT45_BME280: picture update
2024-03-19 PCBs: HB-UNI-SEN-BATT_ATMega1284P_E07-868MS10_FRAM_FUEL4EP: changed validation status in README.md
2024-03-26 PCBs/HB-UNI-SEN-BATT_ATMega1284P_E07-868MS10_FRAM_FUEL4EP/FRAM_test: added serial monitor log
2024-04-02 PCBs: update of validation results of CC1101_868MHz_RF_Modul_FUEL4EP and CC1101_868MHz_UFL_RF_Modul_FUEL4EP: added RSSI sensitivities
2024-04-06 uodate of README.md
2024-04-06 sketches/FreqTest_range_test_with_distant_beacon: documentation updates
2024-04-11 sketches: HB-UNI-Sensor1-THD-SHT45 and HB-UNI-Sensor1-THPD-SHT45_BME280: fixes due to changes of Sensirion library
2024-04-24 sketches: FreqTest_range_test_with_distant_beacon: added hint how to increase frequency resolution of receive characteristics
2024-04-24 PCBs: 4Bit_I2C_Port_Expander_Module_FUEL4EP is now successfully validated; update of README.md; added pictures of prototype
2024-04-28 sketches: HB-UNI-Sensor1-THPD-BME280: update of README.md
2024-05-07 PCBs: HB-UNI-SEN-BATT_ATMega1284P_E07-868MS10_FRAM_FUEL4EP: update of FRAM test
2024-05-27 PCBs: HB-UNI-SEN-BATT_ATMega1284P_E07-868MS10_FRAM_FUEL4EP: updated FRAM_test sketch
2024-06-04 update of AsksinPP_developments/addons/hb-ep-devices-addon/CCU_RM/AsksinPP_addon_files_generator/extract_rftypes_XML.groovy due to change of EQ3's libraries
2024-06-10 Updated HowTos documentation
2024-06-14 deleted fork AsksinPP_developments/libraries/Adafruit_FRAM_SPI
2024-06-14 updated README.md of PCB HB-UNI-SEN-BATT_ATMega1284P_E07-868MS10_FRAM_FUEL4EP
2024-06-19 added new sketch HB-UNI-Sensor1-THP_MA-AHT20_BMP280
2024-06-22 sketches/HB-UNI-Sensor1-THP_MA-AHT20_BMP280: documentation updates
2024-06-25 PCBs: updates to promote Adapter_EByte_E07_900MM10S_to_Ebyte_E07_868MS10_FUEL4EP in several PCBs
2024-06-26 sketches/HB-UNI-Sensor1-THP_MA-AHT20_BMP280: added measurement results of first 7 days as an example
2024-07-05 sketches/HB-UNI-Sensor1-THP_MA-AHT20_BMP280: updates of solar radiation shield
2024-07-07 sketches/HB-UNI-Sensor1-THP_MA-AHT20_BMP280: delete construction data of inner radiation shield due to a necessary reconstruction
2024-07-15 release of new AsksinPP climate change observation sensor HB-UNI-Sensor1-THP_MA-AHT20_BMP280
2024-07-17 sketches/HB-UNI-Sensor1-THP_MA-AHT20_BMP280: added measurement of improved solar radiation shield
2024-07-25 PCBs: CC1101_868MHz_RF_Modul_FUEL4EP and Adapter_EByte_E07_900MM10S_to_Ebyte_E07_868MS10_FUEL4EP: update of documentation
2024-09-13 PCBs/HB-UNI-SenAct-4-4-SC_DS_FUEL4EP: added control possibility by iPAD shortcuts
2024-09-18 sketches/HB-UNI-Sensor1-THP_MA-AHT20_BMP280: added documentation after 3 months of operation: moving averages and battery discharge
2024-09-26 CBs/Adapter_EByte_E07_900MM10S_to_Ebyte_E07_868MS10_FUEL4EP: update of README.md
2024-09-26 PCBs/HB-UNI-SEN-BATT_ATMega1284P_E07-900MM10S_FUEL4EP: migration to KiCAD 8, LCSC fixes; PCBs/HB-UNI-SEN-BATT_ATMega1284P_E07-868MS10_FUEL4EP: BOM update
2024-09-29 PCBs/HB_Stamp_ATMega1284P_FUEL4EP: migration to KiCAD 8
2024-09-29 PCBs/4Bit_I2C_Port_Expander_Module_FUEL4EP: migration to KiCAD 8
2024-09-30 PCBs/I2C_Module_SHT85_BME280: migration to KiCAD 8; fix of DRC rules
2024-09-30 PCBs/CC1101_868MHz_UFL_RF_Modul_FUEL4EP: migration to KiCAD 8
2024-09-30 PCBs/HB-UNI-SEN-BATT_E07-900MM10S_FUEL4EP: migration to KiCAD 8
2024-10-01 added further HowTos/ISP Programmer/Diamex Prog-S2/Linux/avrdude/example scripts
2024-10-29 sketches/HB-UNI-Sensor1-THP_MA-AHT20_BMP280: added note that calculation of the yearly moving average is currently wrong due to a type error resulting in an overflow
2024-11-16 antennas: added 868.3MHz_DIY_dipole_antenna
2024-11-18 antennas: added three wired antennas without GND plane
2024-11-25 sketches/HB-UNI-Sensor1-THP_MA-AHT20_BMP280: release after successful validation of moving average values; bug for 1 year moving averages has successfully been fixed
2024-12-16 sketches/HB-UNI-Sensor1-THPD-SHT45_BME280: added akku discharge curve after 8 months
2025-01-26 PCBs/HB-UNI-SEN-BATT_FUEL4EP: migration to KiCAD 8.0.8-8.0.8-0~ubuntu22.04.1, release build
2025-02-17 added pre-release of PCBs/HB_Stamp_IO_ATMega1284P_FUEL4EP
2025-02-25 upgraded PCBs/HB-UNI-SEN-BATT_FUEL4EP to V1.5 supporting now HB_Pro_Mini_ATMEGA1284P_FUEL4EP
2025-02-27 PCBs: updated some JLCPCB manufacturing data after trial-order
2025-03-06 PCBs/HB_Pro_Mini_ATMEGA1284P_FUEL4EP: update of LCSC data for JLCPCB prototype production
2025-03-13 deleted subfolder 'Bots'; a better solution has been found
2025-03-28 removed all links to hits counter https://hits.seeyoufarm.com/ since this server has been abandoned
2025-04-03 PCBs/HB-UNI-SEN-BATT_FUEL4EP, PCBs/HB_Pro_Mini_ATMEGA1284P_FUEL4EP, and PCBs/I2C_Module_SHT45_BME280_small_FUEL4EP: added notifications about successful validation
2025-04-13 PCBs/HB_Stamp_IO_ATMega1284P_FUEL4EP and PCBs/HB_Stamp_IO_EXT_LEDs_Buttons_FUEL4EP: README.md updates
2025-04-15 PCBs/HB_Stamp_IO_ATMega1284P_FUEL4EP: added avrdude and FreqTest tests and results
2025-04-19 added missing KiCAD libraries
2025-05-07 sketches with Kalman filter: Added note for max. version of BasicLinearAlgebra library: V3.7
2025-05-07 documentation fixes
2025-06-06 HB-UNI-Sensor1-THP_MA-AHT20_BMP280: added improved solar radiation shield
2025-06-22 sketches/HB-UNI-Sensor1-THP_MA-AHT20_BMP280: added note to avoid shadow flicker of the TFA weather protection housing
2025-07-01 measurement results of sketch HB-UNI-Sensor1-THP_MA-AHT20_BMP280 after 6 months operation
2025-10-03 Shorted the maximum path names of repository by 70 characters (from 278 to 208) in order to cope with path name limitations of Window Operating Systems, a mapping file is provided in case shortened f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
2025-11-03 sketches/HB-UNI-Sensor1-THP_MA-AHT20_BMP280: documentation update / README.md: support of openCCU
2026-01-14 PCBs/Adapter_EByte_E07_900MM10S_to_Ebyte_E07_868MS10_FUEL4EP and PCBs/Adapter_EByte_E07_900MM10S_to_noname_green_RF_module_FUEL4EP: documentation updates
2026-04-11 HB-UNI-SEN-BATT_ATMega1284P_E07-900MM10S_CO2_FUEL4EP: added warning in README.md not to uuse because of fatal errors of PCB
